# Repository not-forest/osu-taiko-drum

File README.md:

# 🥁 Osu! Taiko Drum Controller

A cross-platform, DIY **Taiko drum controller** designed for playing **[osu!taiko](https://osu.ppy.sh/home)** on PC. This controller functions as a fully configurable keypad that detects vibration-based hits and maps them to keypress events, serving as a general-purpose input device.

The project includes:

- Hardware schematics and PCB layout  
- Firmware written in Rust using RTIC framework
- GUI interface for configuring the drum from the host side (TODO!)
- Jupyter notebook for simulating piezoelectric sensor signals and modeling post-processing, which is then rewritten within the firmware in no_std environment
- A command-line utility for configuring the drum from the host side.  
- 3D-printable components for building the physical enclosure

---

---

## Visual Overview

- **Assembled Physical Drum Controller**  

- **Electronic Schematic**  

- **PCB Layout**  

---

### Project Overview

---

## Firmware

The firmware is written in Rust using the [RTIC framework](https://rtic.rs/), simulating a general-purpose HID device to ensure compatibility across all major operating systems. It simultaneously exposes a serial interface for configuration and control via utility software.

Each of the four piezoelectric sensors is sampled independently using dedicated ADC channels. The firmware captures both "Don" and "Kat" hits in pairs with minimal latency. Captured samples are fed into a queue and processed by a parser task that performs post-processing to detect real and spurious hits. Inner constants like `sensitivity` and `sharpness` are configurable from the utility software. Valid hits are mapped into keypresses and transmitted as USB HID reports.

All configuration data is stored in the last page of the flash memory and can be updated at runtime using the configuration utility.

---

## Hardware

The custom PCB is designed in KiCad and features core components typically found on “Blue Pill” development boards, including SWD debug headers and an onboard reset button. The controller is powered directly via USB, which also serves as the communication link for HID reports to the host system.

---

## Configuration Utility (TODO! swap to GUI utility)

A lightweight command-line utility written in Tcl is provided for runtime configuration. It allows to:

- Remap keypresses for each sensor. Can be changed to any proper keyboard key.
- Adjust hit detection `sensitivity` and `sharpness` to fine tune inner hit detection algorithm
- Send control commands, such as firmware reboot.
- Firmware update support (TODO!)

---

## 3D Printed Parts

All necessary 3D-printable components are located in the `3d/` directory. This includes:

- Raw Blender model files
- Cura-ready imported `.3mf` files

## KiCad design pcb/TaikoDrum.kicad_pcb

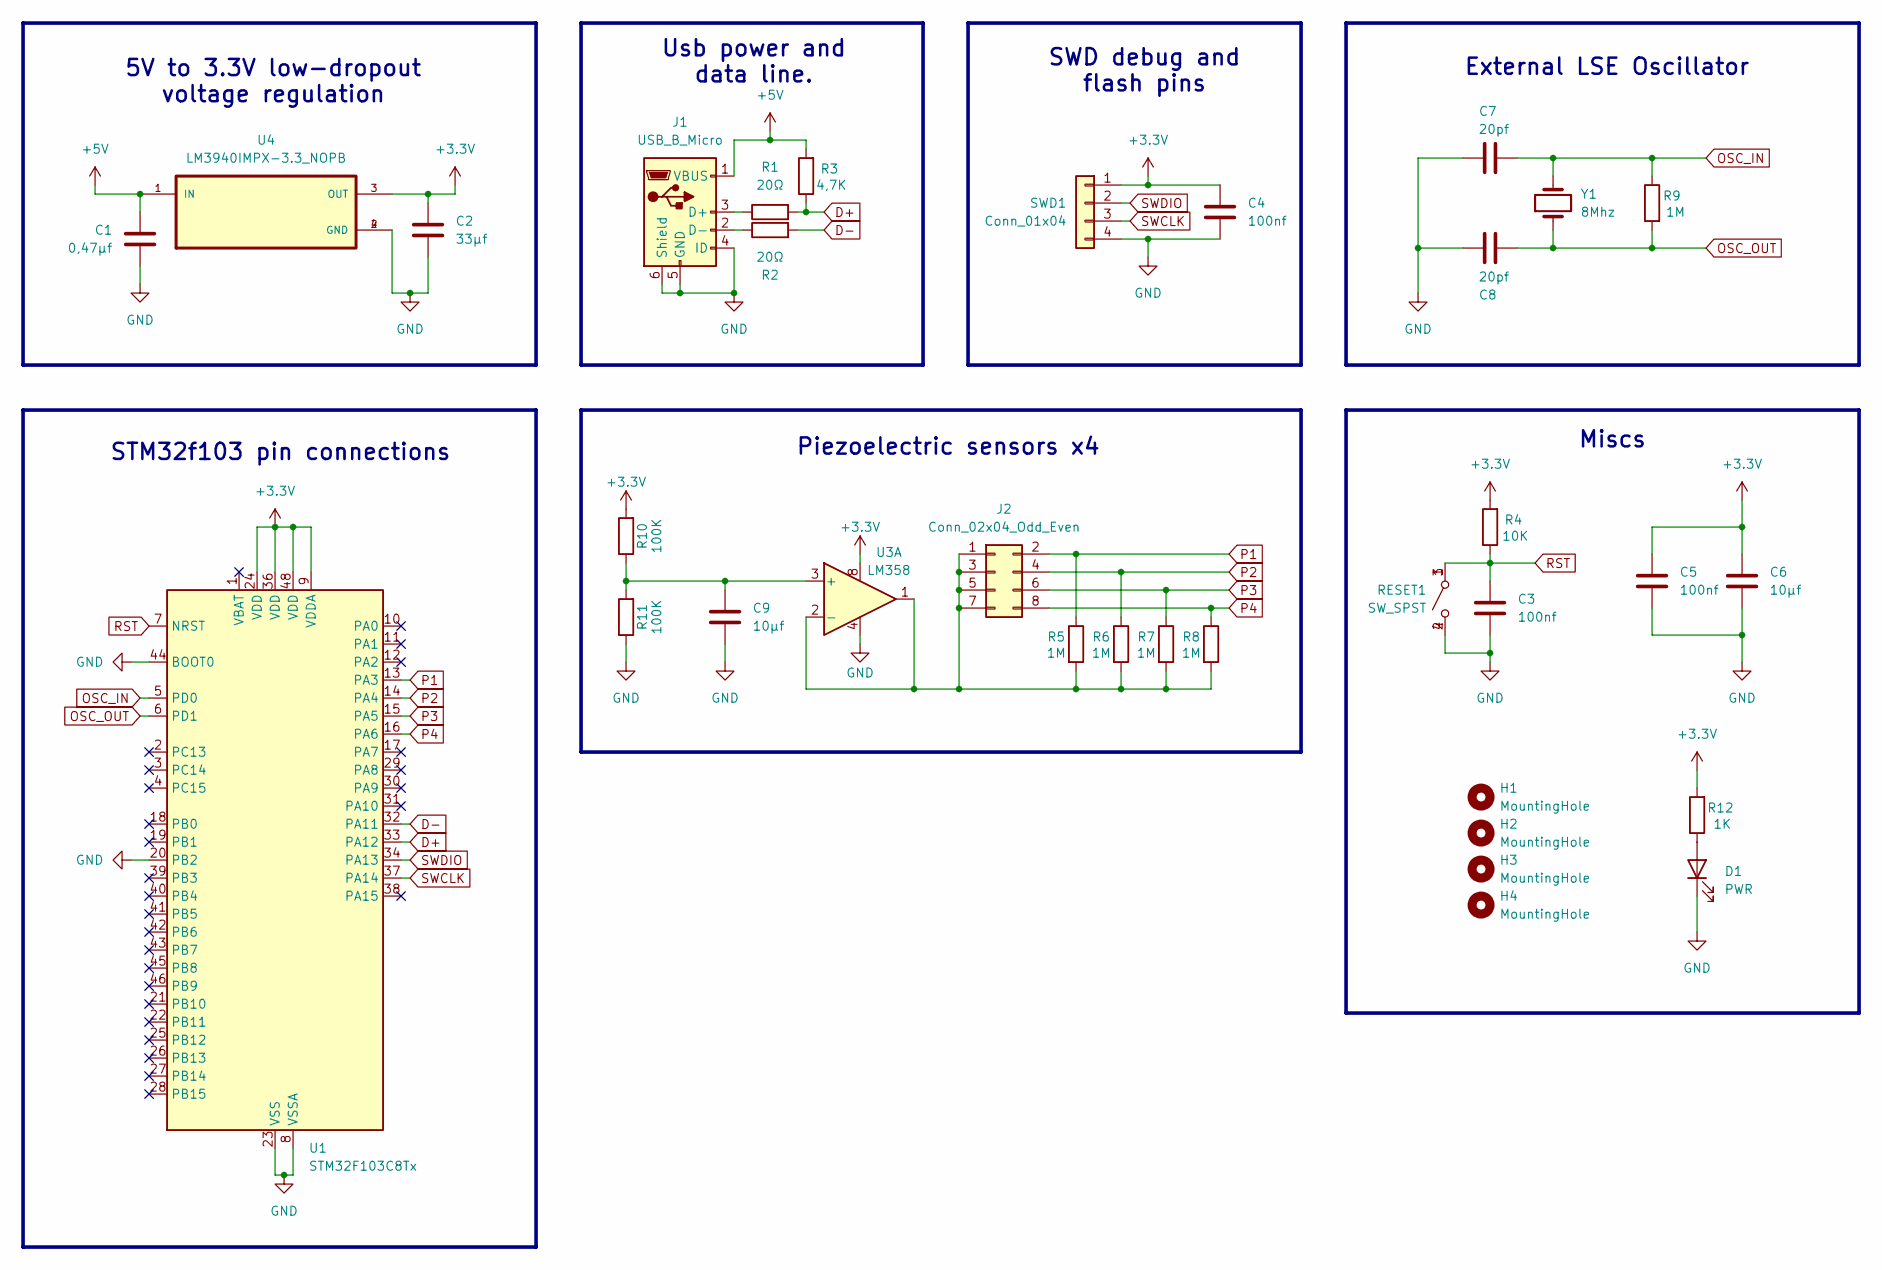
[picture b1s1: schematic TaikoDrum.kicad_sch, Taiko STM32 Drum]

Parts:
C1: 0,47µf; C_Radial_D5.0mm_H5.0mm_P2.00mm
C2: 33µf; C_Radial_D5.0mm_H5.0mm_P2.00mm
C3, C4, C5: 100nf; C_Radial_D5.0mm_H5.0mm_P2.00mm
C6, C9: 10µf; C_Radial_D5.0mm_H5.0mm_P2.00mm
C7, C8: 20pf; C_Radial_D5.0mm_H5.0mm_P2.00mm
D1: PWR; LED_D3.0mm
H1, H2, H3, H4: MountingHole; MountingHole_2.2mm_M2
J1: USB_B_Micro; MICRO-USB-SMD_5P-P0.65-H-F_C10418
J2: Conn_02x04_Odd_Even; PinHeader_2x04_P2.54mm_Vertical
R1, R2: 20Ω; R_Axial_DIN0204_L3.6mm_D1.6mm_P2.54mm_Vertical
R3: 4,7K; R_Axial_DIN0204_L3.6mm_D1.6mm_P2.54mm_Vertical
R4: 10K; R_Axial_DIN0204_L3.6mm_D1.6mm_P2.54mm_Vertical
R5, R6, R7, R8, R9: 1M; R_Axial_DIN0204_L3.6mm_D1.6mm_P2.54mm_Vertical
R10, R11: 100K; R_Axial_DIN0204_L3.6mm_D1.6mm_P2.54mm_Vertical
R12: 1K; R_Axial_DIN0204_L3.6mm_D1.6mm_P2.54mm_Vertical
RESET1: SW_SPST; SW_FSM8JH
SWD1: Conn_01x04; PinHeader_1x04_P2.54mm_Vertical
U1: STM32F103C8Tx; LQFP-48_7x7mm_P0.5mm
U3: LM358; DIP-8_W7.62mm
U4: LM3940IMPX-3.3_NOPB; SOT230P700X180-4N
Y1: 8Mhz; Crystal_HC52-U_Vertical

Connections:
+3.3V: C2.1, C4.1, C5.1, C6.1, R4.2, R10.2, R12.2, SWD1.1, U1.9 (VDDA), U1.24 (VDD), U1.36 (VDD), U1.48 (VDD), U3.8, U4.3 (OUT)
+5V: C1.1, J1.1 (VBUS), R3.2, U4.1 (IN)
D+: R1.2, R3.1, U1.33 (PA12)
D-: R2.2, U1.32 (PA11)
GND: C1.2, C2.2, C3.2, C4.2, C5.2, C6.2, C7.1, C8.1, C9.2, D1.1 (K), J1.4 (ID), J1.5 (GND), J1.6 (Shield), R11.1, RESET1.2 (B), RESET1.4 (B), SWD1.4, U1.8 (VSSA), U1.20 (PB2), U1.23 (VSS), U1.35 (VSS), U1.44 (BOOT0), U1.47 (VSS), U3.4, U4.2 (GND), U4.4 (GND)
unnamed: D1.2 (A), R12.1
unnamed: J1.3 (D+), R1.1
unnamed: J1.2 (D-), R2.1
unnamed: J2.1, J2.3, J2.5, J2.7, R5.2, R6.2, R7.2, R8.2, U3.1, U3.2 (-)
unnamed: C9.1, R10.1, R11.2, U3.3 (+)
OSC_IN: C7.2, R9.1, U1.5 (PD0), Y1.2
OSC_OUT: C8.2, R9.2, U1.6 (PD1), Y1.1
P1: J2.2, R5.1, U1.13 (PA3)
P2: J2.4, R6.1, U1.14 (PA4)
P3: J2.6, R7.1, U1.15 (PA5)
P4: J2.8, R8.1, U1.16 (PA6)
RST: C3.1, R4.1, RESET1.1 (A), RESET1.3 (A), U1.7 (NRST)
SWCLK: SWD1.3, U1.37 (PA14)
SWDIO: SWD1.2, U1.34 (PA13)

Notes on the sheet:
STM32f103 pin connections
Piezoelectric sensors x4
5V to 3.3V low-dropout voltage regulation
Usb power and data line.
Miscs
SWD debug and flash pins
External LSE Oscillator

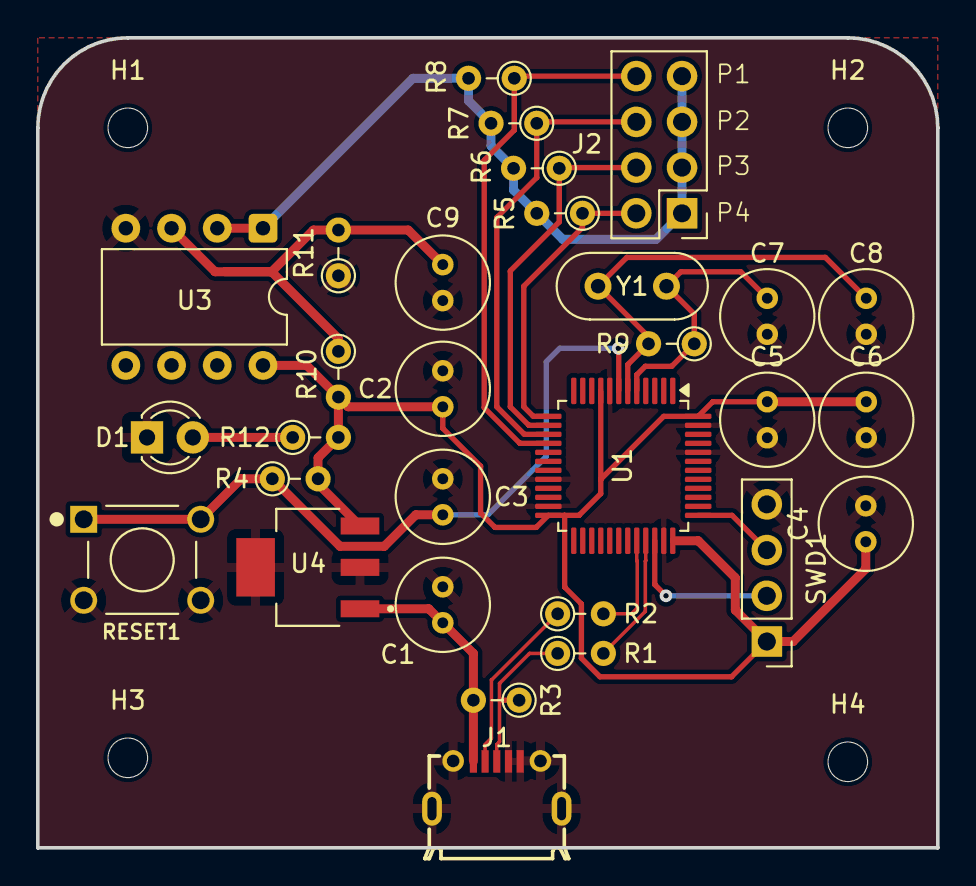
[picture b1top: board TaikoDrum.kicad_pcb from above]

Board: 2 copper layers, 50.0 x 45.0 mm, 34 parts (0 on the bottom side), 19 nets.

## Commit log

2025-04-05 First PCB skeleton with USB-STM32f103 connection and voltage regulation.
2025-04-06 Creates RTIC project skeleton for STM32F103 microcontroller.
2025-04-06 Added implementation for application logger. TODO! Add additional logging to report file for future sending via USB connection to the host laptop from the drum.
2025-04-06 Added main application files with initialized RTIC environment.
2025-04-06 Switched to RTICv2.
2025-04-07 Added single core critical section feature for M3
2025-04-07 Logging module now called 'logger' to not confuse with log crate.
2025-04-07 RTIC application functionality is completely moved to main library file. Initialized Systick monotonic for general purpose use.
2025-04-07 Completed the first theoretical schematic prototype.
2025-04-08 Added rtic-sync for monotonic implementations.
2025-04-09 Added module for handling piezoelectric sensor data from selected analog pins simultaneously via two ADC's working in master-slave mode with injected channels used to sample center and edge drum hits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
2025-04-09 Added external oscillator and decouplers for the Taiko Drum circuit.
2025-04-10 Added 16M resistor for external LSE oscillator according to the STM32F103 errata recomendations.
2025-04-10 Properly initialized injected simultaneous mode for ADC1, ADC2.
2025-04-11 Added first blank implementation of USB HID support for the Taiko Drum Firmware. Moved version related data to custom module.
2025-04-12 Added device information strings. Serial number is being generated based from md5 hash based on the current firmware version.
2025-04-15 Built more robust USB firmware handling.
2025-04-15 Added Embed logging support.
2025-04-16 Minor changes to RCC related. comments
2025-04-16 Detecting a proper USB device on the host machine. Fixed the USB peripheral to obtain a proper 48 MHz clock signal and PCLK1 to be larger than 8MHz. Additional initialization polling is done to allow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
2025-04-17 Added better initialization polling handling during device's start. Separated the gpio disconection part to allow future reconnection from other parts of the firmware.
2025-04-17 Now only perform init polling check on low-priority interrupt. Better error handling for HID report test.
2025-04-17 Removed the need of mutable static UsbAllocator<_> and the use of unsafe features by putting the allocator into the local variable of the init function. This also ensures that the new function will o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
2025-04-18 Interrupt free initialization allows for faster USB enumeration.
2025-04-19 Added configuration TCL script to configure the device via USB serial interface.
2025-04-22 Using last flash page as a configuration storage for Taiko Drum. This storage will hold information about mapped keypresses and signal processing settings.
2025-04-25 Added serial port for future configurability and firmware update flashing.
2025-04-25 Conventional names.
2025-04-25 Added first skeleton for drum parser. Now sender task will only be used when a change of state is seen by the parser task. Added additional task skeleton for serial port.
2025-04-25 Splitted the hid module into separate HID and USB parts for readibility.
2025-04-25 Removed the unecessary baud rate argument.
2025-04-27 Added reset command. Added alias for read command.
2025-04-30 Added raw 3D models, Cura sliced models and G-Code for Taiko Drum
2025-05-01 Stand model update.
2025-05-01 Implemented programmer to handle firmware configuration and provide external control from the utility software. Moved monotonics after the clock initialization for better readibility.
2025-05-01 Used an additional voltage divider to not loose any energy from the piezo signal.
2025-05-04 Added first version of parser algorith with dynamic energy-based thresholding. Only works on a singular channel for now. (Very unstable).
2025-05-06 Using RTIC reexport for blocking USB critical section part.
2025-05-06 Swapped static parser key mappings to those used in current configuration.
2025-05-06 Completed the proper implementation of one channel piezoelectric parser detecting with adaptive thresholding. Made parser configuration dynamic and savable in the flash alongside ky mappings.
2025-05-06 Swapped to individual adaptive threshold for each piezo channel. Improved HID report sending and reduced latency.
2025-05-07 Updated PCB schematic.
2025-05-08 Fixed all programming commands. Providing proper data type conversion for upcoming bytes.
2025-05-08 Fixed programmer not being able to obtain CPU cycles due to rapid interrupts. Implemented fully working reading procedure. TODO! fix writing procedure to obtain byte-by-byte data.
2025-05-09 Better LM358 based op-amp buffering for piezo voltage dividers.
2025-05-10 Improved the schematic design with shared buffer for all four piezos and extra decoupling. Created first PCB design with all required components for THT soldering (except for STM32).
2025-05-13 Added docs. Modified README.
2025-05-14 Fixed wrong USB wiring. Removed unecessary marks.
2025-05-14 Better diff line routing. Additional dev text.
2025-05-20 Fixed sharpness configuration programming method.
2025-05-20 Added icon.
2025-05-30 Fixed microcontroller GNDing.
2025-06-22 Fixed all paths within the controller design. Swapped the micro USB footprint with JLCPCB compatible for auto assembly. Fixed clearance.
2025-07-06 Silkscreen names for SWD pads are now named correctly.
2025-07-06 Updated the code according to new borrowing requirements by rustc.
2025-07-07 Fixed the D+ line. the PCB schematic and layout is now 100% fully workable design. Fixed the button connection to be compatible with most generic tactile switches.
2025-07-11 Updated docs with newest schematics/PCB
2025-10-03 Added simulation Jupyter sheets to find an optimal solution to cross-talk problem and then implement it within the parser on low-level.
2025-10-03 Slight changes in parser implementation. Do not use energies anymore because they provide completely chaotic results during fast hits and loose delay information just like FFT. Using deviation as a f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
2025-10-04 First implementation of cross-talk detection with FFT-based cross-correlation function.
2025-10-06 Fixing the sample window structure. Adjusted window length to fit flash's size properly without affecting USBD definitions in .bss sector. Made cross-correlation filtering little bit better. May requ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
